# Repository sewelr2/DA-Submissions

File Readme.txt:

Ryan Sewell 

8000473785

sewelr2@unlv.nevada.edu

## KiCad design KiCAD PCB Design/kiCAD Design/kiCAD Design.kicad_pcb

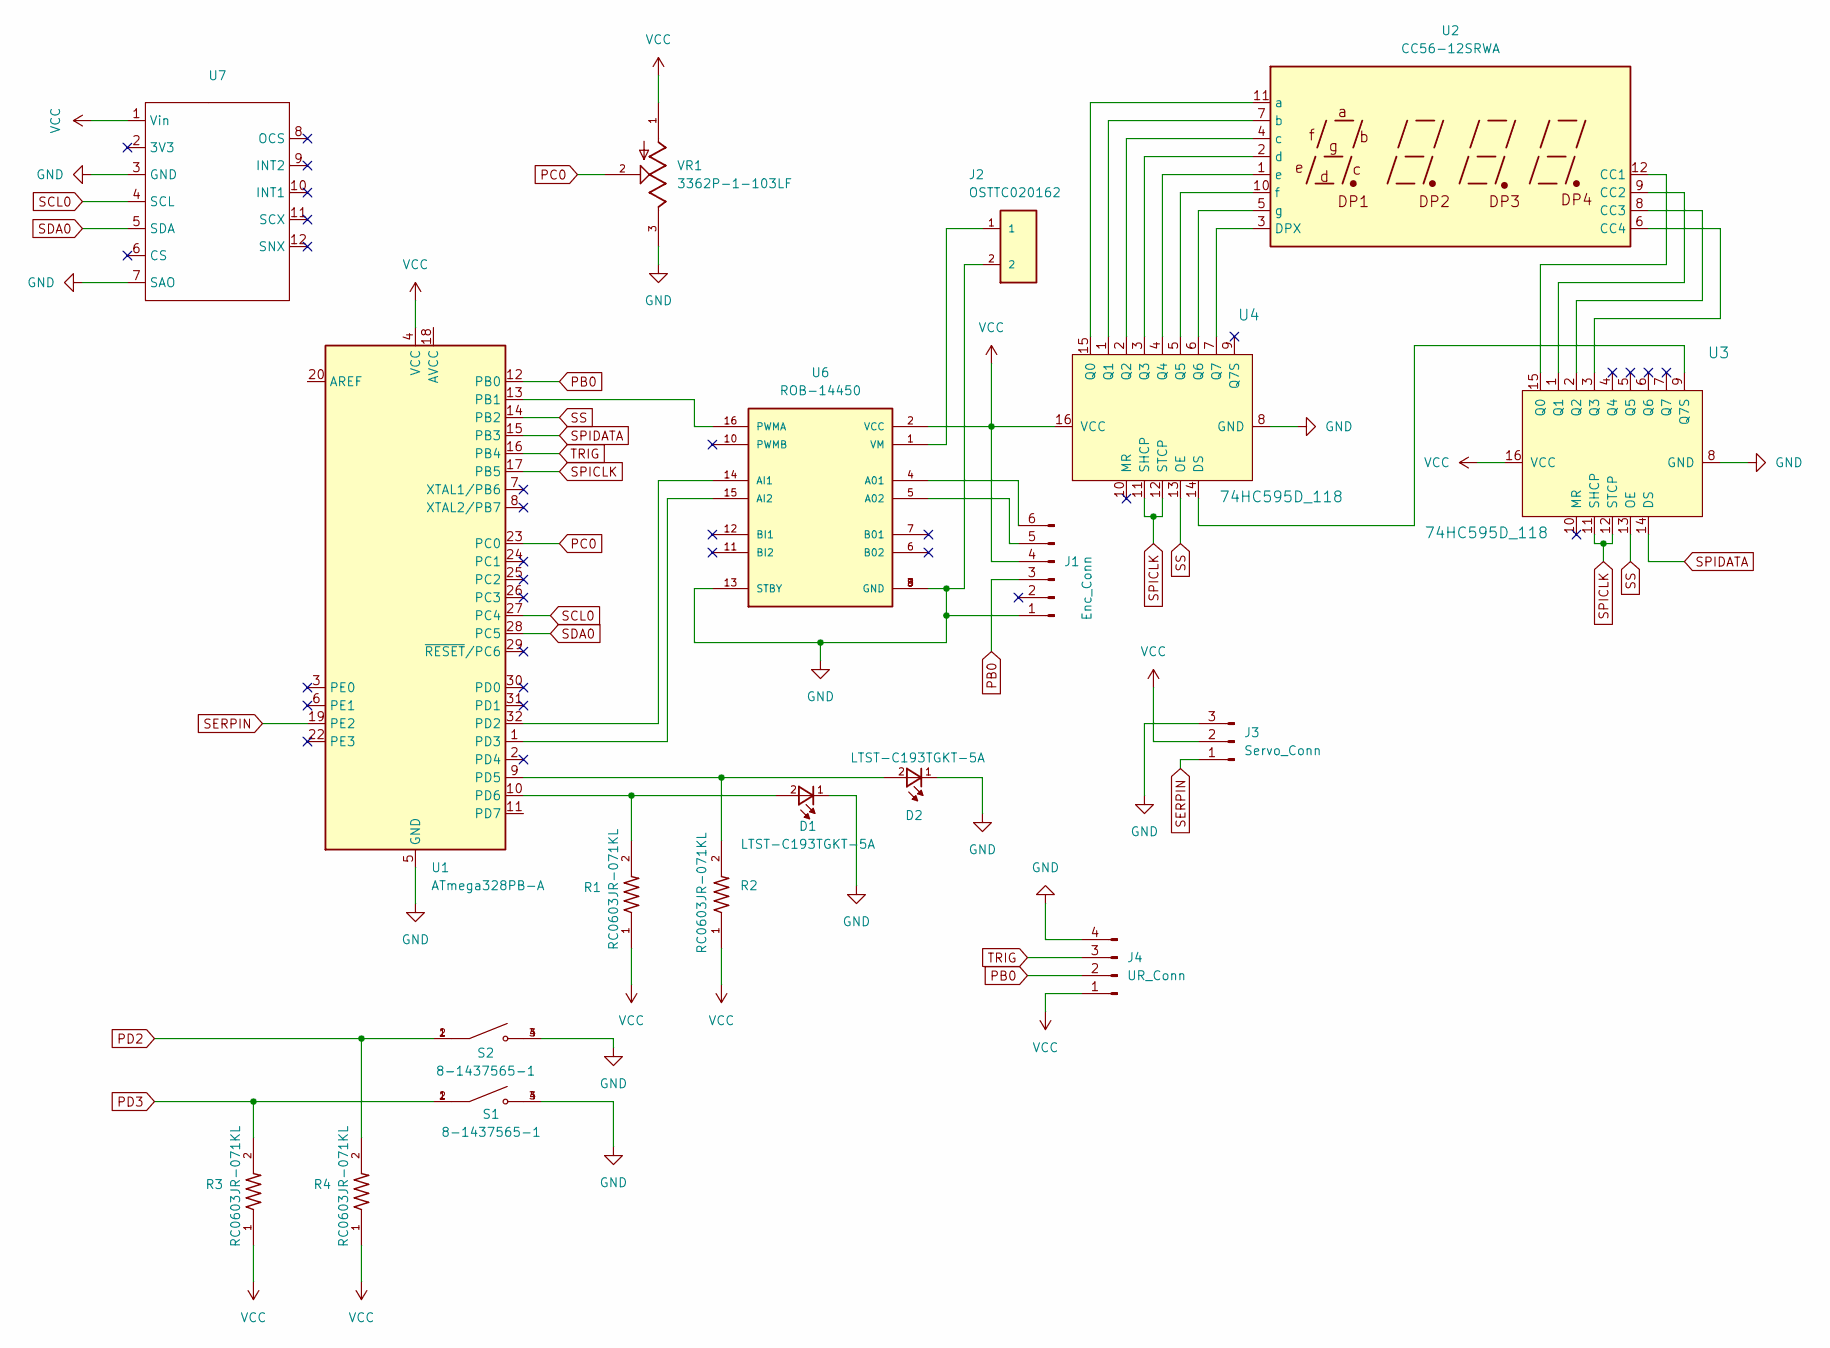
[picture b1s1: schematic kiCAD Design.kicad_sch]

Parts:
D1, D2: LTST-C193TGKT-5A; 0603
J1: Enc_Conn; PinHeader_1x06_P2.54mm_Vertical
J2: OSTTC020162; OST_OSTTC020162
J3: Servo_Conn; PinHeader_1x03_P2.54mm_Vertical
J4: UR_Conn; PinHeader_1x04_P2.54mm_Vertical
R1, R2, R3, R4: RC0603JR-071KL; RESC1607X60N
S1, S2: 8-1437565-1; SW_8-1437565-1; PARTREV H3
U1: ATmega328PB-A; TQFP-32_7x7mm_P0.8mm
U2: CC56-12SRWA; CA56-12SRWA
U3, U4: 74HC595D_118; SOIC-16_W3.90mm; MPN 74HC595D,118; Digi-Key_PN 1727-2821-1-ND
U6: ROB-14450; MODULE_ROB-14450; PARTREV 11-13-17
U7: BMI160
VR1: 3362P-1-103LF; TRIM_3362P-1-103LF; PARTREV 08/26/10

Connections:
GND: D1.1, D2.1, J1.1, J2.2, J3.3, J4.4, S1.3, S1.4, S2.3, S2.4, U1.5 (GND), U1.21 (GND), U3.8 (GND), U4.8 (GND), U6.3 (GND), U6.8 (GND), U6.9 (GND), U6.13 (STBY), U7.3 (GND), U7.7 (SAO), VR1.3
unnamed: J1.5, U6.5 (A02)
unnamed: J1.6, U6.4 (A01)
unnamed: U1.13 (PB1), U6.16 (PWMA)
unnamed: U1.32 (PD2), U6.14 (AI1)
unnamed: U1.1 (PD3), U6.15 (AI2)
unnamed: D2.2, R2.2, U1.9 (PD5)
unnamed: D1.2, R1.2, U1.10 (PD6)
unnamed: U2.12 (CC1), U3.15 (Q0)
unnamed: U2.9 (CC2), U3.1 (Q1)
unnamed: U2.8 (CC3), U3.2 (Q2)
unnamed: U2.6 (CC4), U3.3 (Q3)
unnamed: U2.3 (DPX), U4.7 (Q7)
unnamed: U2.11 (a), U4.15 (Q0)
unnamed: U2.7 (b), U4.1 (Q1)
unnamed: U2.4 (c), U4.2 (Q2)
unnamed: U2.2 (d), U4.3 (Q3)
unnamed: U2.1 (e), U4.4 (Q4)
unnamed: U2.10 (f), U4.5 (Q5)
unnamed: U2.5 (g), U4.6 (Q6)
unnamed: U3.9 (Q7S), U4.14 (DS)
unnamed: J2.1, U6.1 (VM)
PB0: J1.3, J4.2, U1.12 (PB0)
PC0: U1.23 (PC0), VR1.2
PD2: R4.2, S2.1, S2.2
PD3: R3.2, S1.1, S1.2
SCL0: U1.27 (PC4), U7.4 (SCL)
SDA0: U1.28 (PC5), U7.5 (SDA)
SERPIN: J3.1, U1.19 (PE2)
SPICLK: U1.17 (PB5), U3.11 (SHCP), U3.12 (STCP), U4.11 (SHCP), U4.12 (STCP)
SPIDATA: U1.15 (PB3), U3.14 (DS)
SS: U1.14 (PB2), U3.13 (OE), U4.13 (OE)
TRIG: J4.3, U1.16 (PB4)
VCC: J1.4, J3.2, J4.1, R1.1, R2.1, R3.1, R4.1, U1.4 (VCC), U3.16 (VCC), U4.16 (VCC), U6.2 (VCC), U7.1 (Vin), VR1.1

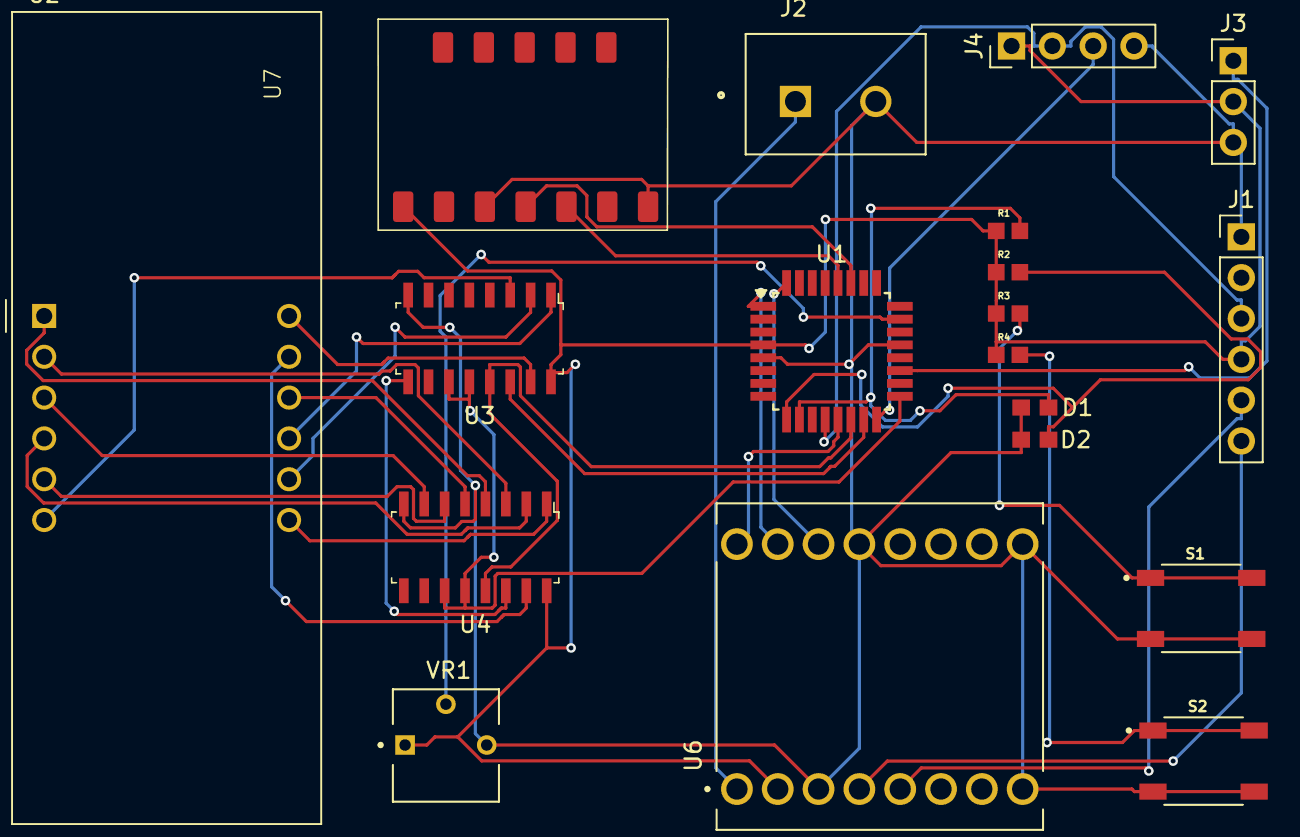
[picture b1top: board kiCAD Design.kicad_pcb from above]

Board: 2 copper layers, 19 parts (0 on the bottom side), 34 nets.
